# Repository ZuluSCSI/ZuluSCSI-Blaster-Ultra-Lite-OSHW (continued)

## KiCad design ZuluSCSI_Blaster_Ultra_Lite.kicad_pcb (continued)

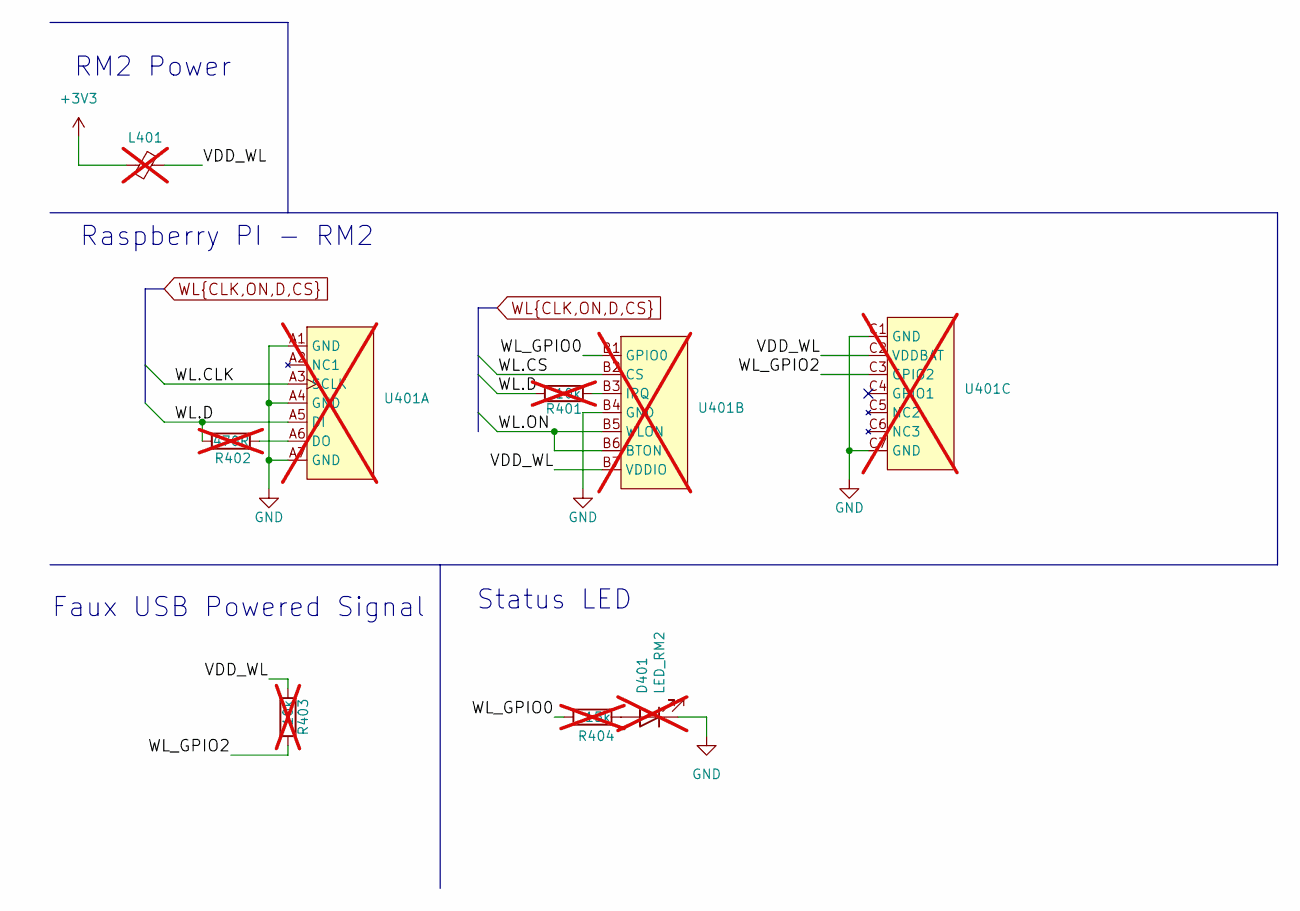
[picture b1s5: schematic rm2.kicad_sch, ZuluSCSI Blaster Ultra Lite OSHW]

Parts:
D401: LED_RM2; LED_0805_2012Metric; LCSC C2297; not fitted
L401: Ferrite_Bead_Small; L_0603_1608Metric; PartNumber BLM18PG330SN1D; LCSC C88984; not fitted
R401, R403: 10k; R_0603_1608Metric; PartNumber RC0603FR-0710KL; LCSC C25804; not fitted
R402: 470R; R_0603_1608Metric; PartNumber RC0603FR-07470RL; LCSC C23179; not fitted
R404: 15k; R_0603_1608Metric; PartNumber RC0603FR-0715KL; LCSC C22809; not fitted
U401: RPI_RM2; PartNumber RMC20452T; LCSC C49451547; not fitted

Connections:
+3V3: L401.2; also elsewhere on the board
/RM2/VDD_WL: L401.1, R403.2, U401.B7 (VDDIO), U401.C2 (VDDBAT)
/RM2/WL_GPIO0: R404.2, U401.B1 (GPIO0)
/RM2/WL_GPIO2: R403.1, U401.C3 (GPIO2)
GND: D401.1 (K), U401.A1 (GND), U401.A4 (GND), U401.A7 (GND), U401.B4 (GND), U401.C1 (GND), U401.C7 (GND); also elsewhere on the board
unnamed: D401.2 (A), R404.1
unnamed: R402.2, U401.A6 (DO)
unnamed: R401.2, U401.B3 (IRQ)
WL.CLK: U401.A3 (SCLK); also elsewhere on the board
WL.CS: U401.B2 (CS); also elsewhere on the board
WL.D: R401.1, R402.1, U401.A5 (DI); also elsewhere on the board
WL.ON: U401.B5 (WLON), U401.B6 (BTON); also elsewhere on the board

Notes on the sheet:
Faux USB Powered Signal
Raspberry PI - RM2
Status LED
RM2 Power

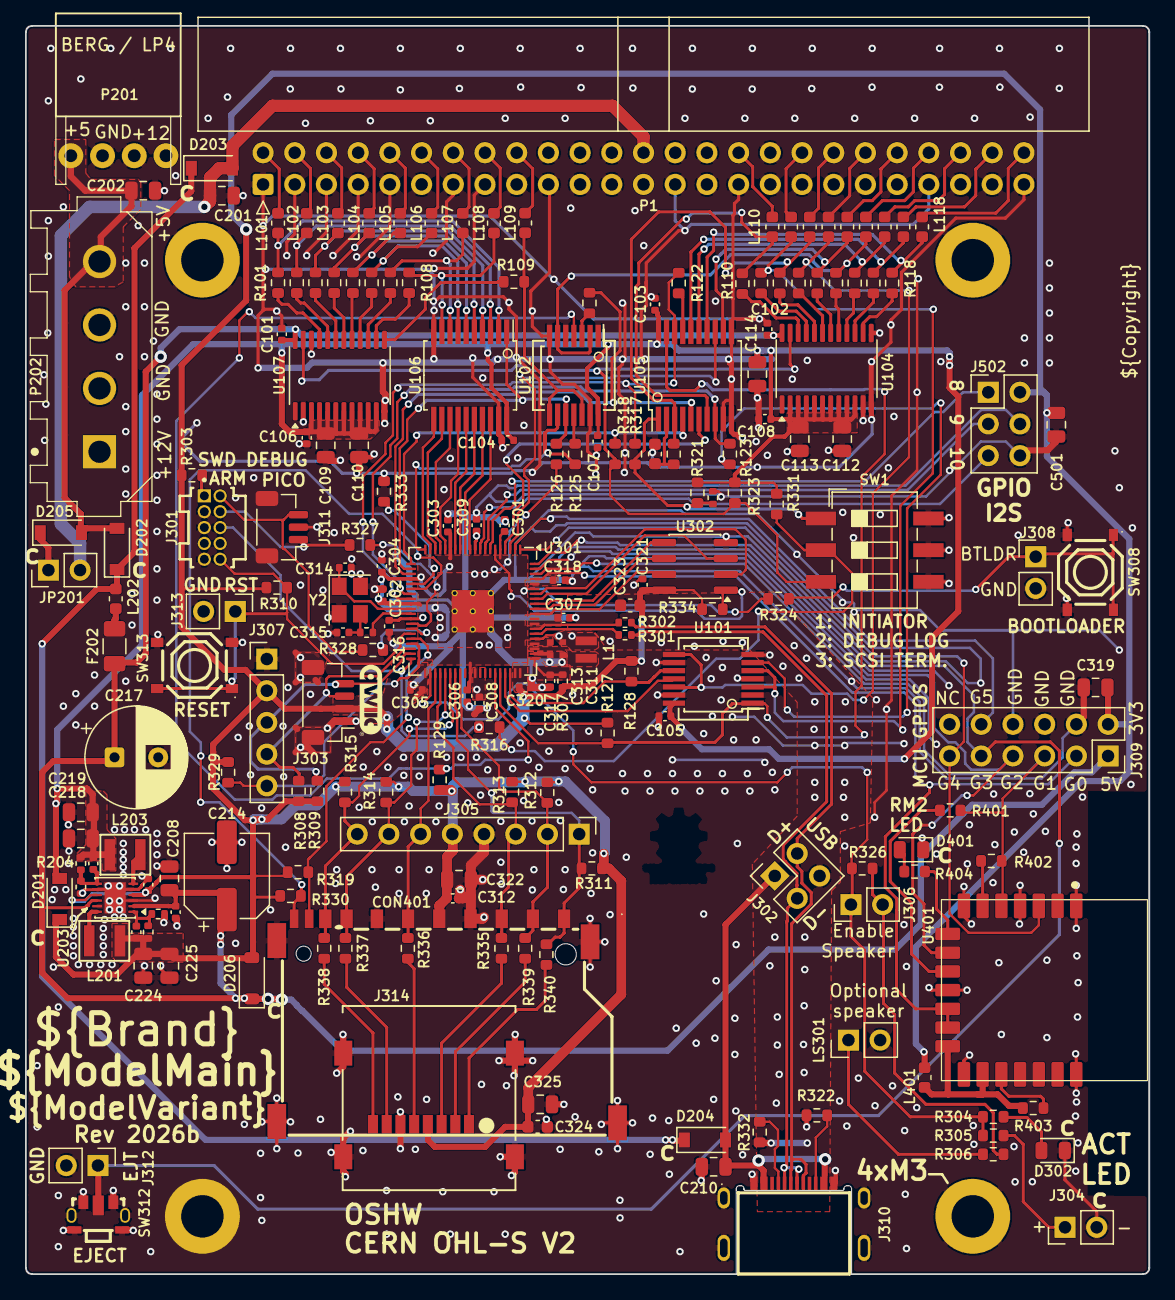
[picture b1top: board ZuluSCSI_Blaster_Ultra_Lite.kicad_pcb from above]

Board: 2 copper layers, 90.0 x 100.0 mm, 202 parts (1 on the bottom side), 161 nets.
